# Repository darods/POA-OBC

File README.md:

# Pillar of Autumn OBC

The purpose of this project is to give the knowledge and open source code on how to build a flight computer (On Board Computer (OBC)) for an amateur model rocket for research and science projects.

The Arduino code is in the *OBC directory*, and it's divided in subfiles for ease of use. To run it you have to compile de **OBC.ino** file.

## What i does?
Is a simple data logger that stores the values of the sensors in a CSV file for further analysis. Is also activate a servo motor when detects free fall for a parachute deployment mechanism.

*POA is an achronym of "Pillar Of Autumn", the coolest spaceship of Halo Reach*

## How it stores data?
The method for storing info is in the *logData.ino* file. The order in wich is save is:
1. logTime: time passed since it's turn on
2. Relative altitude.
3. Free fall state: 0 or 1
4. BMP280 temperature
5. Pressure
6. Pitch
7. Roll
8. Yaw
9. X Acceleration
10. Y Acceleration
11. Z Acceleration

### Libraries
For running this project, you will have to download some libraries for arduino :
* [SdFat](https://github.com/greiman/SdFat) - by Bill Greiman
* [MPU6050](https://github.com/jarzebski/Arduino-MPU6050) - by Korneliusz Jarzebski (improved version [here](https://github.com/el-NASA/Arduino-MPU6050))
* [BMP280](https://github.com/adafruit/Adafruit_BMP280_Library) - by Adafruit (if you use a chinese version you should change the I2C address from 0x77 to 0x76)

## Schematics and PCB design
The **OBC** use the MPU6050 and BMP280 Sensors, a micro SD module and a buzzer for alerts. It also has the capability to activate a servo motor when it dectects free fall.

I hope that the information in this repository is a good starting point for your science and technology projects, If you want to help us developing this, feel free to do it.

## References
* Calamac Projects (2015). “Arduino Rocket Data Logger”. Instructables.com. Recuperado de: https://www.instructables.com/id/Arduino-Rocket-Data-Logger
* Boyarizo E. y Méndez C. (2017). Diseño y construcción de un microsatélite(CanSat). IES El Burgo de Las Rozas.
* Day B., Lumpkin T., Huegele V., Pierce C. (Sin fecha). “Basics of rocketry”. Huntsville Area Rocketry Assiciation (HARA).
* Newton M. (2012). Rocket Anatomy 101. NAR.
* Orlando J. (2012). “Estudio de la trayectoria de un cohete de tres etapas lanzado desde el territorio colombiano”. Universidad Nacional de Colombia, Bogotá. Pag. 80-81.
* T. Benson (2014). Brief History of Rockets. NASA. Recuperado de : https://www.grc.nasa.gov/www/k-12/TRC/Rockets/history_of_rockets.html
* Van Milligan T. (2009) “Make a rocket payload bay”. Apogee Rockets. Recuperado de : https://www.youtube.com/watch?v=_ctUCO8GsJ4&index=30&list=PLnX-NFLCOOVkq82xIrfm6KuaVoljTCtob
* Van Milligan T. (Sin fecha). “Pressure Relief Holes”. Apogee preak of flight newsletter, issue 68.

### Bibliography
* Álvarez N., Huérfano R., Ojeda O., (2015) “Diseño e implementación de misión para el lanzamiento de un cohete para tres kilómetros de altura”. Universidad Nacional de Colombia, Bogotá.
* Esero (sin fecha). “2018 UK Cansat Competition Guidelines”. Esero. Pag. 9-10.
* European Space Agency(ESA) (2018). “CanSat Guidelines 2018-109”. ESA.
* Ojeda O. (2016) “The Aerospace development and research group of the Universidad Nacional de Colombia, GIDA-UN. A tool for aerospace education in Colombia”. 67 th International Astronautical Congress (IAC). México, Guadalajara.
* Ricardo P. (2018). “Reto de innovación IEEE 2018 – CanSat para la paz”. Universidad Distrital. Bogotá. Recuperado de : https://ieee.udistrital.edu.co/ieee-innovation-2018/

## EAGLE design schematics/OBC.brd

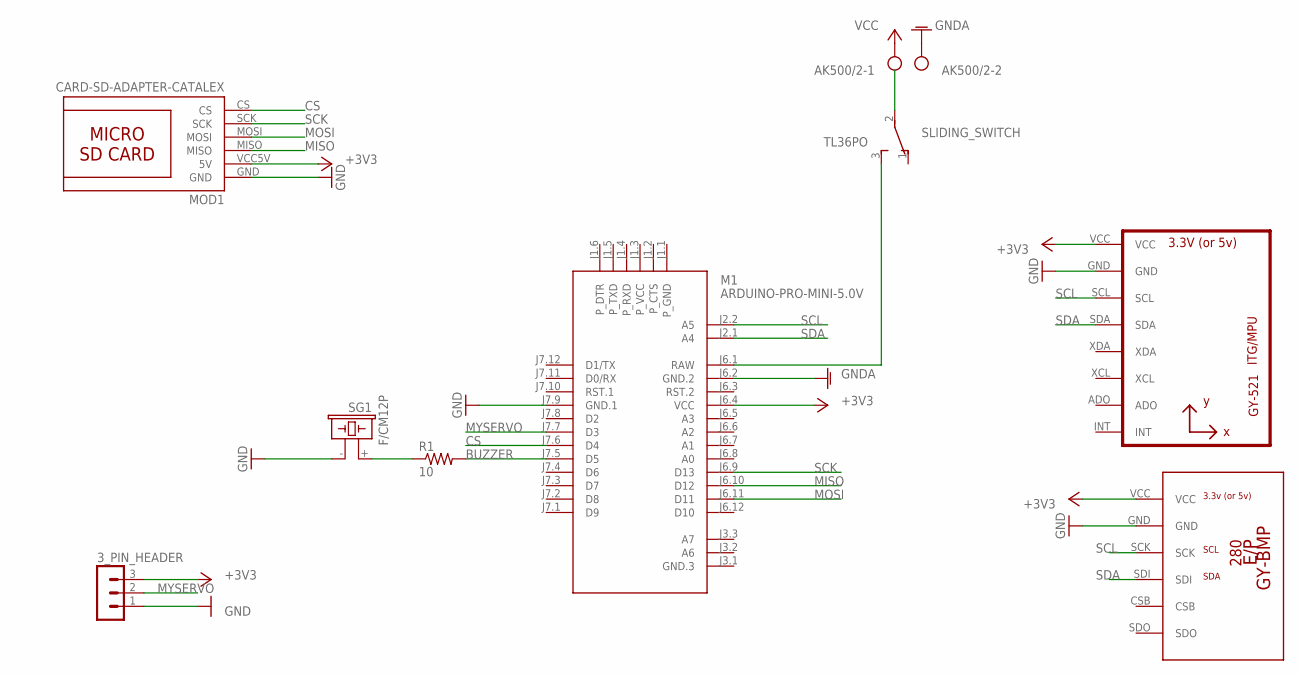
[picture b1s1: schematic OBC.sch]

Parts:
3_PIN_HEADER: MA03-1
AK500/2: AK500/2
M1: ARDUINO-PRO-MINI-5.0V; ARDUINO-PRO-MINI
MOD1: CARD-SD-ADAPTER-CATALEX
R1: 10; 0204/7
SG1: F/CM12P
SLIDING_SWITCH: TL36PO; TL3XPO
U1: GY-521MPU6050; GY-521
U$1: GY-BPM280; GY-BMP280-FOOTPRINT

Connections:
+3V3: 3_PIN_HEADER.3, M1.J6.4 (VCC), MOD1.VCC5V (5V), U1.VCC, U$1.VCC
BUZZER: M1.J7.5 (D5), R1.2
CS: M1.J7.6 (D4), MOD1.CS
GND: 3_PIN_HEADER.1, M1.J7.9 (GND.1), MOD1.GND, SG1.- (2), U1.GND, U$1.GND
GNDA: AK500/2.2, M1.J6.2 (GND.2)
MISO: M1.J6.10 (D12), MOD1.MISO
MOSI: M1.J6.11 (D11), MOD1.MOSI
MYSERVO: 3_PIN_HEADER.2, M1.J7.7 (D3)
unnamed: M1.J6.1 (RAW), SLIDING_SWITCH.3 (S)
unnamed: R1.1, SG1.+ (1)
SCK: M1.J6.9 (D13), MOD1.SCK
SCL: M1.J2.2 (A5), U1.SCL, U$1.SCK
SDA: M1.J2.1 (A4), U1.SDA, U$1.SDI
VCC: AK500/2.1

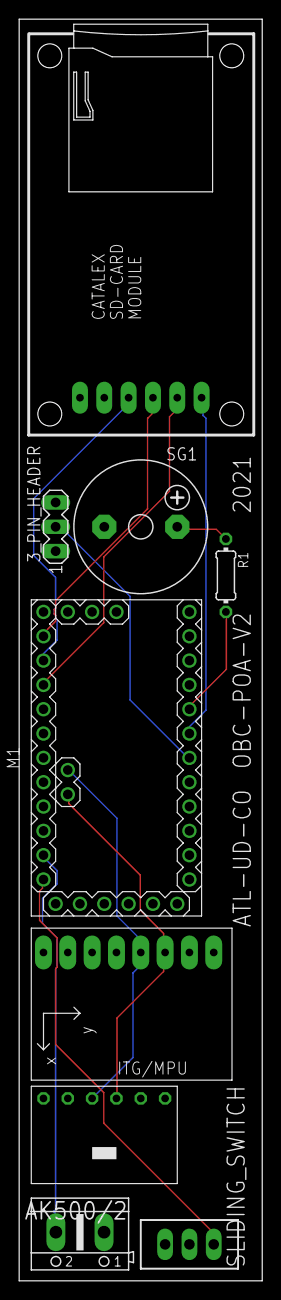
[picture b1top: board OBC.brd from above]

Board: 2 copper layers, 25.4 x 131.8 mm, 9 parts (0 on the bottom side), 13 nets.

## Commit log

2018-06-14 Version 1.00
2018-06-14 la puta madre
2018-06-14 vamos a ver
2018-06-15 Version 1.02
2018-06-15 Version 1.03
2018-06-15 Version 2.0
2018-06-15 Version 2.1
2018-06-18 Version 3.0
2018-06-18 Version 3.1
2018-07-17 Version 3.2
2018-07-17 Version 3.3
2018-07-21 Version 3.4
2018-07-24 Version 3.5
2018-07-25 Version 3.6
2018-07-26 Version 2.2
2018-07-26 Version 3.6.1
2018-07-26 Version 3.6.2
2018-07-26 Version 4.0
2018-07-30 version 4.01
2018-07-30 Version 4.02
2018-07-30 Version 4.03
2018-08-12 Version 4.1
2018-08-14 Version 4.2
2018-08-15 Version 4.3
2018-08-19 se unieron
2018-08-19 Master+Alternative
2018-09-04 MA 1.01
2018-11-03 MA 1.02
2018-11-28 Cambiando de pc
2018-11-29 preparando una mejora de almacenamiento
2018-11-29 se cambio el baud rate, se añadio un tiempo de espera de 50 milis y se comento lo del piezo buzzer
2018-11-29 cambios al codigo de ejemplo
2018-11-30 se cambio el nombre del documento
2018-11-30 Añadiendo ejemplo xbee
2018-12-09 mejora en la capacidad de fuerza g y resolucion del ms5611
2018-12-09 version estable con arreglos
2018-12-11 Se añadio el nuevo codigo de la segunda computadora de vuelo
2018-12-11 Se quito la caida libre y se puso la micro SD
2018-12-11 se añadio caida libre
2018-12-11 Se añadio la notificacion de caida libre sin afectar mucho al rendimiento total
2018-12-11 Version estable con caida libre
2018-12-11 sigo arreglando errores
2018-12-11 Creo que solucione los errores de merge
2018-12-11 poniendo led caida libre
2018-12-16 Añadiendo mas datos a flycomputer y corrigiendo guardado de datos en flycomputer2
2018-12-17 no me acuerdo del cambio
2018-12-18 cambios al baudrate de fly1
2018-12-18 Adicion codigo sd a fly 2 y cambio del baudrate
2018-12-21 Se arreglo error de corrupciond de datos, se quito luz led caida libre
2018-12-22 en proceso de arreglo de cogido flycomputer, hay un error persistente en la altura del sensor MS5811
2018-12-22 se creo un nuevo archivo cuyo proposito es mejorar el desmpeño de la primera computadora de vuelo que tiene como IMU el sensor GY-86, el nombre de este archivo es fly1
2018-12-23 Se añadio flyi2c cuyo proposito es mejorar el rendimiento del codigo al evitar usar librerias para los sensores
2018-12-23 se hizo la conversion de fuerzas g a m/s2, ademas se dejo comentado el codio para mostrar pitch, roll y yaw, pero el valor de yaw no da buenos resultados
2018-12-23 primeros ensayos i2c con el sensor MS5611
2018-12-23 Create LICENSE
2018-12-23 Se modificaron los nombres de los archivos se organizaron algunos
2018-12-24 Se movio sensoresunidocaida libre a la carpeta de computadoras en desarrollo y se cambio su nombre a SensoresUnidos
2018-12-24 Añadiendo librerias necesarias para la ejecucion de los codigos
2018-12-24 añadiendo intrucciones para las lbrarias
2018-12-26 Nueva simulacion con el cohte recortado, arhivo llamado POA(recortado), donde se analiza el rendimiento de 3 motores y ademas el desempeño del cohete recortado
2019-01-05 Adelanto en flight computer1 sin incluir la libreria mpu6050
2019-01-05 se elimino la carpeta de referencias de codigo para que el repositorio no fuera tan pesado
2019-01-05 fixed some issues posted in issue#12 by Koepel, the recomendations were implemented in MS5611.cpp and flyMPU6050
2019-01-05 Fixed MPU6050.cpp according to koepel in issue#12
2019-01-08 Added some changes in flMS5611.ino suggested by koepel in the issue
2019-01-08 Fixed the issue that involved the functions fastRegister8 and readRegister8 posted by koepel,also i kind of fixed the alititude given by MS5611 in FlightComputer1.ino
2019-01-08 Found an easy to understand code for SdFat library
2019-01-09 Working on an optimization for the flightcomputer1.ino using SdFat library, current work in FlightComputer1SDFat.ino
2019-01-09 Sd improvement works fine! it improve the code from 82% in programm memory usage over to 72% and Dinamic memory improved from 62% to 59%, there is only one problem with normAccel.Zaxis value
2019-01-09 Working very nice, the code for the flightcomputer1 has major improvements, memory usage go from 82% to 77% and dynamic memory stays the same, 62%, but now it records yaw and free fall
2019-01-09 It works pretty good, flightcomputer1 has major improvements, reduction in memory usage and dynamic memory as well, now it records yaw and free fall, can be stop from loging data and has no time rest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
2019-01-15 Cleaning some files
2019-02-09 added the improvments to the flight computer that has the bmp280 instead of the MS5611
2019-08-01 borrados archivos sin uso y añadida nueva simulacion con solo la OBC
2019-08-01 Se mejoró el readme
2019-08-07 actualizando
2019-08-08 modificado para hacer el cansat
2019-08-11 puesto un delay y muestra el tiempo transcurrido
2019-08-19 puesto delay codigo cansat
2019-08-20 hecho el diagrama de cableado y pcb para el cansat
2019-08-20 en proceso de actualizacion diagrama OBC
2019-08-21 cambios cansat codigo
2019-08-23 cambios en el diseño pcb
2019-09-05 proceso correcion pcb
2019-10-29 añadido buzzer
2019-10-30 reemplazadas alertas serial por alertas con buzzer
2019-11-01 modificando la 2 version de la OBC, quitando BT
2019-11-01 removido el BT de la 2 OBC, reemplazada por alertas buzzer
2019-11-13 un pequeño error
2019-11-13 añadido diseño 3D del mecanismo de recuperación
2019-11-13 movido documentos del cansat
2019-11-13 añadido codigo servo y la pieza del seguro de este
2020-01-20 better readme, deleated unnecessary files and folders. Added new images
2020-01-20 Added gitignore
2021-03-18 primera parte de la limpieza
2021-03-18 deleting no relevant directories and files
2021-03-19 updated licence
2021-03-19 added licence
2021-03-19 added 3D models

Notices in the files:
parts and their libraries:
diy-modules: Released under the Creative Commons Attribution 4.0 International License: http://creativecommons.org/licenses/by/4.0
